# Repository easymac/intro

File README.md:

# Intro

Semi-ergo layout inspired by [/mtei/SemiErgo_Layout](https://github.com/mtei/SemiErgo_Layout).

Split, open source, low profile, wireless, 68 keys.

Unfinished & untested.

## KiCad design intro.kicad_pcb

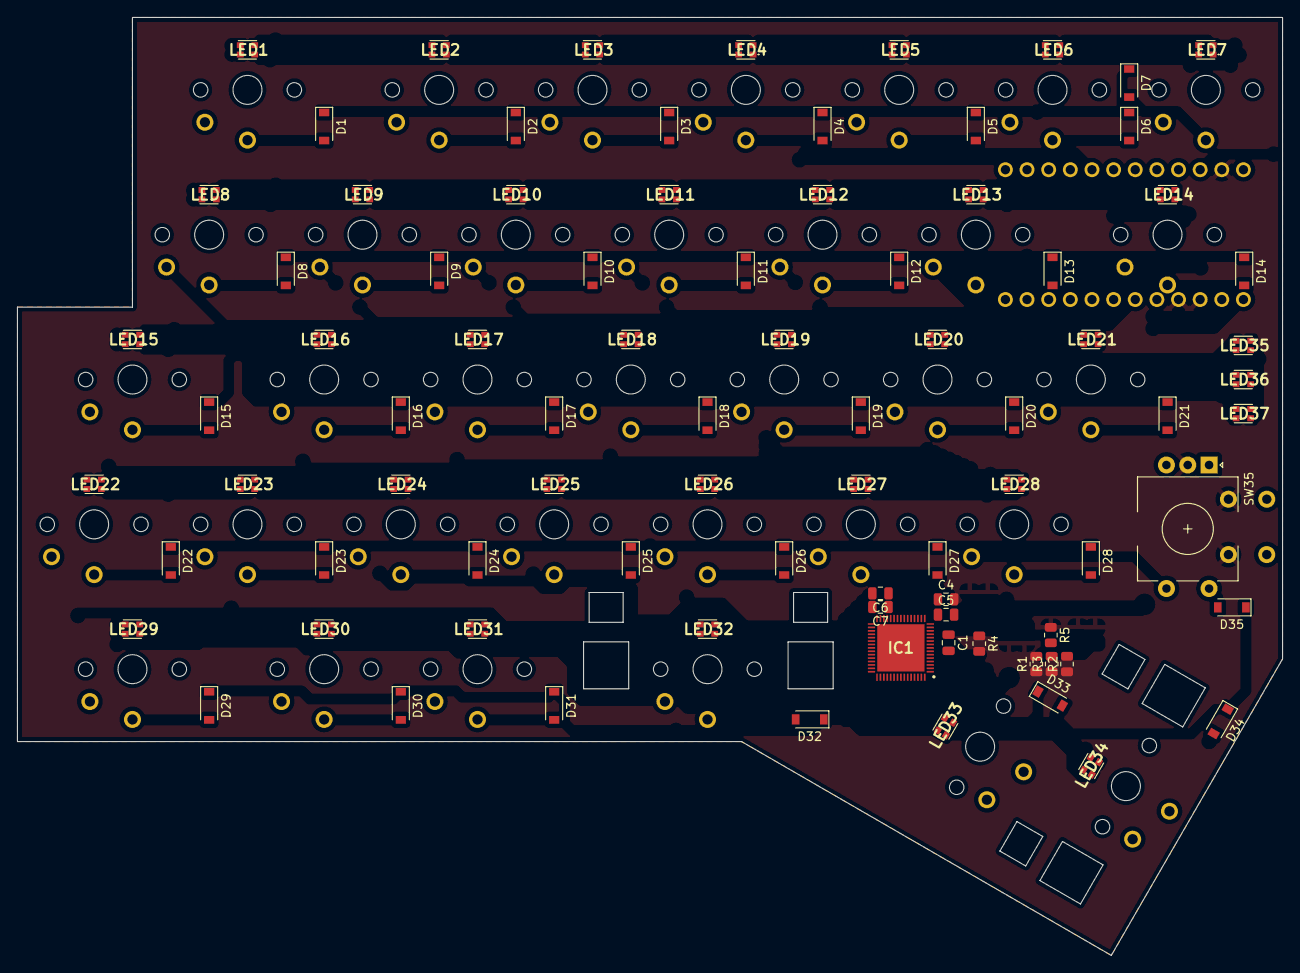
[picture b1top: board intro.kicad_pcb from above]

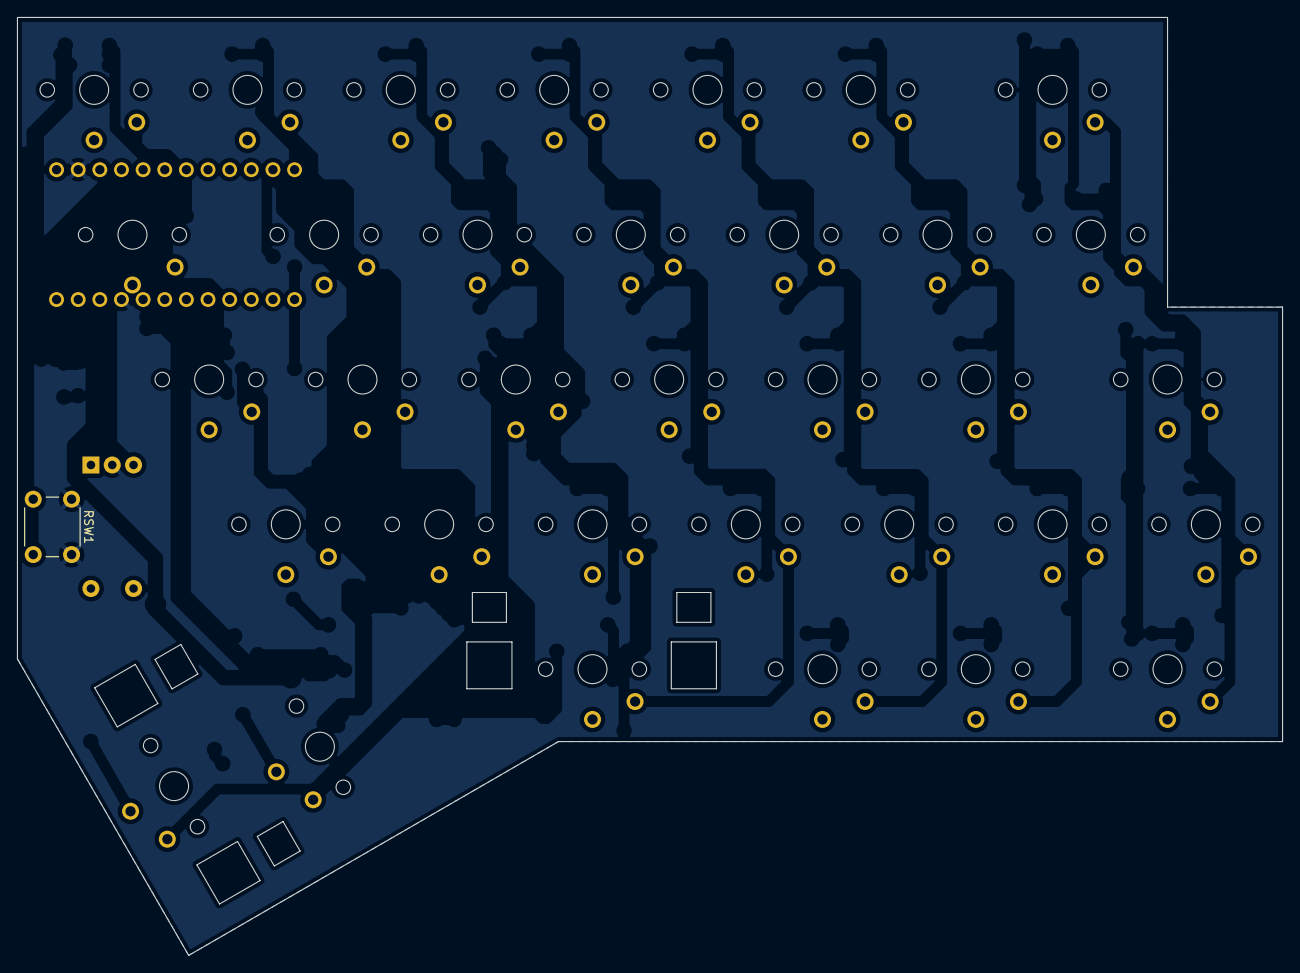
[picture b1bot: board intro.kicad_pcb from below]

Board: 2 copper layers, 148.5 x 110.1 mm, 122 parts (2 on the bottom side), 83 nets, no tracks yet.

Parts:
C1, C5, C7: 0.1μF; C_0805_2012Metric
C4, C6: 1μF; C_0805_2012Metric
D1, D2, D3, D4, D5, D6, D7, D8, D9, D10, D11, D12, D13, D14, D15, D16, D17, D18, D19, D20, D21, D22, D23, D24, D25, D26, D27, D28, D29, D30, D31, D32, D33, D34, D35: 1N4148W; D_SOD-123
IC1: IS31FL3741A-QFLS4-TR; QFN40P700X700X80-61N-D
LED1, LED2, LED3, LED4, LED5, LED6, LED7, LED8, LED9, LED10, LED11, LED12, LED13, LED14, LED15, LED16, LED17, LED18, LED19, LED20, LED21, LED22, LED23, LED24, LED25, LED26, LED27, LED28, LED29, LED30, LED31, LED32, LED33, LED34, LED35, LED36, LED37: LED_RBAG; FMB2020RGBAHG
R1, R4: 100kΩ; R_0805_2012Metric
R2, R3: 2kΩ; R_0805_2012Metric
R5: 10kΩ; R_0805_2012Metric
RSW1: SW_RST; SW_PUSH_6mm_H4.3mm
S1, S2: Choc_stab; Kailh-PG1350-2u-STAB
SW1, SW14, SW15, SW29, SW33: SW_Push; SW_choc_1.5u
SW2, SW3, SW4, SW5, SW6, SW7, SW8, SW9, SW10, SW11, SW12, SW13, SW16, SW17, SW18, SW19, SW20, SW21, SW22, SW23, SW24, SW25, SW26, SW27, SW28, SW30, SW31, SW32, SW34: SW_Push; SW_choc_1u
SW35: RotaryEncoder_Switch; RotaryEncoder_Alps_EC11E-Switch_Vertical_H20mm_modified
U1: nice_nano; nice_nano_reduced

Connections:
CS1: IC1.26 (CS1), LED1.3 (A), LED15.3 (A)
CS2: IC1.27 (CS2), LED2.3 (A), LED16.3 (A)
CS3: IC1.28 (CS3), LED3.3 (A), LED17.3 (A)
CS4: IC1.29 (CS4), LED4.3 (A), LED18.3 (A)
CS5: IC1.30 (CS5), LED5.3 (A), LED19.3 (A)
CS6: IC1.32 (CS7), LED6.3 (A), LED20.3 (A)
CS7: IC1.31 (CS6), LED7.3 (A), LED21.3 (A)
CS8: IC1.40 (CS14), LED8.3 (A), LED22.3 (A)
CS9: IC1.39 (CS13), LED9.3 (A), LED23.3 (A)
CS10: IC1.38 (CS12), LED10.3 (A), LED24.3 (A)
CS11: IC1.37 (CS11), LED11.3 (A), LED25.3 (A)
CS12: IC1.35 (CS10), LED12.3 (A), LED26.3 (A)
CS13: IC1.34 (CS9), LED13.3 (A), LED27.3 (A)
CS14: IC1.33 (CS8), LED14.3 (A), LED28.3 (A)
CS15: IC1.44 (CS18), LED29.3 (A), LED35.3 (A)
CS16: IC1.43 (CS17), LED30.3 (A), LED36.3 (A)
CS17: IC1.42 (CS16), LED31.3 (A), LED37.3 (A)
CS18: IC1.41 (CS15), LED32.3 (A)
CS19: IC1.45 (CS19), LED33.3 (A)
CS20: IC1.46 (CS20), LED34.3 (A)
ENCA: SW35.A, U1.19 (AIN5/P0.29)
ENCB: SW35.B, U1.18 (AIN0/P0.02)
GND: C1.2, C4.2, C5.2, C6.2, C7.2, IC1.8 (ADDR), IC1.12 (GND_1), IC1.36 (GND_2), IC1.55 (GND_3), IC1.61 (EP), R4.2, R5.1, RSW1.1, SW35.C, U1.3 (GND), U1.4 (GND), U1.23 (GND)
INTB: IC1.7 (INTB), R1.2, U1.5 (P0.17)
unnamed: D1.2 (A), SW1.2
unnamed: D2.2 (A), SW2.2
unnamed: D3.2 (A), SW3.2
unnamed: D4.2 (A), SW4.2
unnamed: D5.2 (A), SW5.2
unnamed: D6.2 (A), SW6.2
unnamed: D7.2 (A), SW7.2
unnamed: D8.2 (A), SW8.2
unnamed: D9.2 (A), SW9.2
unnamed: D10.2 (A), SW10.2
unnamed: D11.2 (A), SW11.2
unnamed: D12.2 (A), SW12.2
unnamed: D13.2 (A), SW13.2
unnamed: D14.2 (A), SW14.2
unnamed: D15.2 (A), SW15.2
unnamed: D16.2 (A), SW16.2
unnamed: D17.2 (A), SW17.2
unnamed: D18.2 (A), SW18.2
unnamed: D19.2 (A), SW19.2
unnamed: D20.2 (A), SW20.2
unnamed: D21.2 (A), SW21.2
unnamed: D22.2 (A), SW22.2
unnamed: D23.2 (A), SW23.2
unnamed: D24.2 (A), SW24.2
unnamed: D25.2 (A), SW25.2
unnamed: D26.2 (A), SW26.2
unnamed: D27.2 (A), SW27.2
unnamed: D28.2 (A), SW28.2
unnamed: D29.2 (A), SW29.2
unnamed: D30.2 (A), SW30.2
unnamed: D31.2 (A), SW31.2
unnamed: D32.2 (A), SW32.2
unnamed: D33.2 (A), SW33.2
unnamed: D34.2 (A), SW34.2
unnamed: IC1.13 (ISET), R5.2
RESET: RSW1.2, U1.22 (RST)
RSW1: IC1.17 (SW2), LED15.2 (BK), LED16.2 (BK), LED17.2 (BK), LED18.2 (BK), LED19.2 (BK), LED20.2 (BK), LED21.2 (BK), LED22.2 (BK), LED23.2 (BK), LED24.2 (BK), LED25.2 (BK), LED26.2 (BK), LED27.2 (BK), LED28.2 (BK), LED29.2 (BK), LED30.2 (BK), LED31.2 (BK), LED32.2 (BK), LED33.2 (BK), LED34.2 (BK)
RSW2: IC1.18 (SW3), LED15.4 (GK), LED16.4 (GK), LED17.4 (GK), LED18.4 (GK), LED19.4 (GK), LED20.4 (GK), LED21.4 (GK), LED22.4 (GK), LED23.4 (GK), LED24.4 (GK), LED25.4 (GK), LED26.4 (GK), LED27.4 (GK), LED28.4 (GK), LED29.4 (GK), LED30.4 (GK), LED31.4 (GK), LED32.4 (GK), LED33.4 (GK), LED34.4 (GK)
RSW3: IC1.16 (SW1), LED15.1 (RK), LED16.1 (RK), LED17.1 (RK), LED18.1 (RK), LED19.1 (RK), LED20.1 (RK), LED21.1 (RK), LED22.1 (RK), LED23.1 (RK), LED24.1 (RK), LED25.1 (RK), LED26.1 (RK), LED27.1 (RK), LED28.1 (RK), LED29.1 (RK), LED30.1 (RK), LED31.1 (RK), LED32.1 (RK), LED33.1 (RK), LED34.1 (RK)
RSW4: IC1.20 (SW5), LED1.2 (BK), LED2.2 (BK), LED3.2 (BK), LED4.2 (BK), LED5.2 (BK), LED6.2 (BK), LED7.2 (BK), LED8.2 (BK), LED9.2 (BK), LED10.2 (BK), LED11.2 (BK), LED12.2 (BK), LED13.2 (BK), LED14.2 (BK), LED35.2 (BK), LED36.2 (BK), LED37.2 (BK)
RSW5: IC1.19 (SW4), LED1.4 (GK), LED2.4 (GK), LED3.4 (GK), LED4.4 (GK), LED5.4 (GK), LED6.4 (GK), LED7.4 (GK), LED8.4 (GK), LED9.4 (GK), LED10.4 (GK), LED11.4 (GK), LED12.4 (GK), LED13.4 (GK), LED14.4 (GK), LED35.4 (GK), LED36.4 (GK), LED37.4 (GK)
RSW6: IC1.21 (SW6), LED1.1 (RK), LED2.1 (RK), LED3.1 (RK), LED4.1 (RK), LED5.1 (RK), LED6.1 (RK), LED7.1 (RK), LED8.1 (RK), LED9.1 (RK), LED10.1 (RK), LED11.1 (RK), LED12.1 (RK), LED13.1 (RK), LED14.1 (RK), LED35.1 (RK), LED36.1 (RK), LED37.1 (RK)
SCL: IC1.10 (SCL), R2.2, U1.2 (RX1/P0.08)
SDA: IC1.9 (SDA), R3.2, U1.1 (TX0/P0.06)
SDB: C1.1, IC1.11 (SDB), R4.1, U1.20 (AIN7/P0.31)
SW35A: SW7.1, SW14.1, SW21.1, SW28.1, SW35.S1, U1.12 (P1.06)
SW35B: D35.2 (A), SW35.S2
VCC: C4.1, C5.1, C6.1, C7.1, IC1.14 (AVCC), IC1.15 (PVCC_1), IC1.25 (PVCC_2), R1.1, R2.1, R3.1, U1.21 (VCC)
col0: SW1.1, SW8.1, SW15.1, SW22.1, SW29.1, U1.6 (P0.20)
col1: SW2.1, SW9.1, SW16.1, SW23.1, SW30.1, U1.7 (P0.22)
col2: SW3.1, SW10.1, SW17.1, SW24.1, SW31.1, U1.8 (P0.24)
col3: SW4.1, SW11.1, SW18.1, SW25.1, SW32.1, U1.9 (P1.00)
col4: SW5.1, SW12.1, SW19.1, SW26.1, SW33.1, U1.10 (P0.11)
col5: SW6.1, SW13.1, SW20.1, SW27.1, SW34.1, U1.11 (P1.04)
row0: D1.1 (K), D2.1 (K), D3.1 (K), D4.1 (K), D5.1 (K), D6.1 (K), D7.1 (K), U1.13 (NFC1/P0.09)
row1: D8.1 (K), D9.1 (K), D10.1 (K), D11.1 (K), D12.1 (K), D13.1 (K), D14.1 (K), U1.14 (NFC2/P0.10)
row2: D15.1 (K), D16.1 (K), D17.1 (K), D18.1 (K), D19.1 (K), D20.1 (K), D21.1 (K), U1.15 (P1.11)
row3: D22.1 (K), D23.1 (K), D24.1 (K), D25.1 (K), D26.1 (K), D27.1 (K), D28.1 (K), U1.16 (P1.13)
row4: D29.1 (K), D30.1 (K), D31.1 (K), D32.1 (K), D33.1 (K), D34.1 (K), D35.1 (K), U1.17 (P1.15)

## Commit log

2022-05-11 Add readme
2022-05-13 Begin improving bypass caps
2022-05-13 Set up LED routing
2022-05-15 Wiring switches & diodes
2022-05-17 Initial LED routing
2022-05-18 WIP: Additonal progress
2022-05-20 Progress
2022-05-20 ... what
2022-05-22 Add front-side SMD C/D/R
2022-05-22 Start rear-side CMD C/D/R
2022-05-22 I hate everything.
2022-05-22 remove traces and vias
2022-06-02 Initial split setup
2022-06-03 Horizontal routing start
